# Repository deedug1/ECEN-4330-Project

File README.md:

# ECEN 4330 Project
Files for ECEN 4330 Project

### Source code
All source code is contained in *main_c.c*.

### PCB design files
Schematics and Board files for the PCB can be found under the *Schematics* folder.

### Documentation
Documentation of the project goals and procedures can be found in the PDF labeled *JustinPachlProjectPaper.PDF*.

*University of Nebraska Lincoln*
*Department of Electrical and Computer Engineering (ECE)*

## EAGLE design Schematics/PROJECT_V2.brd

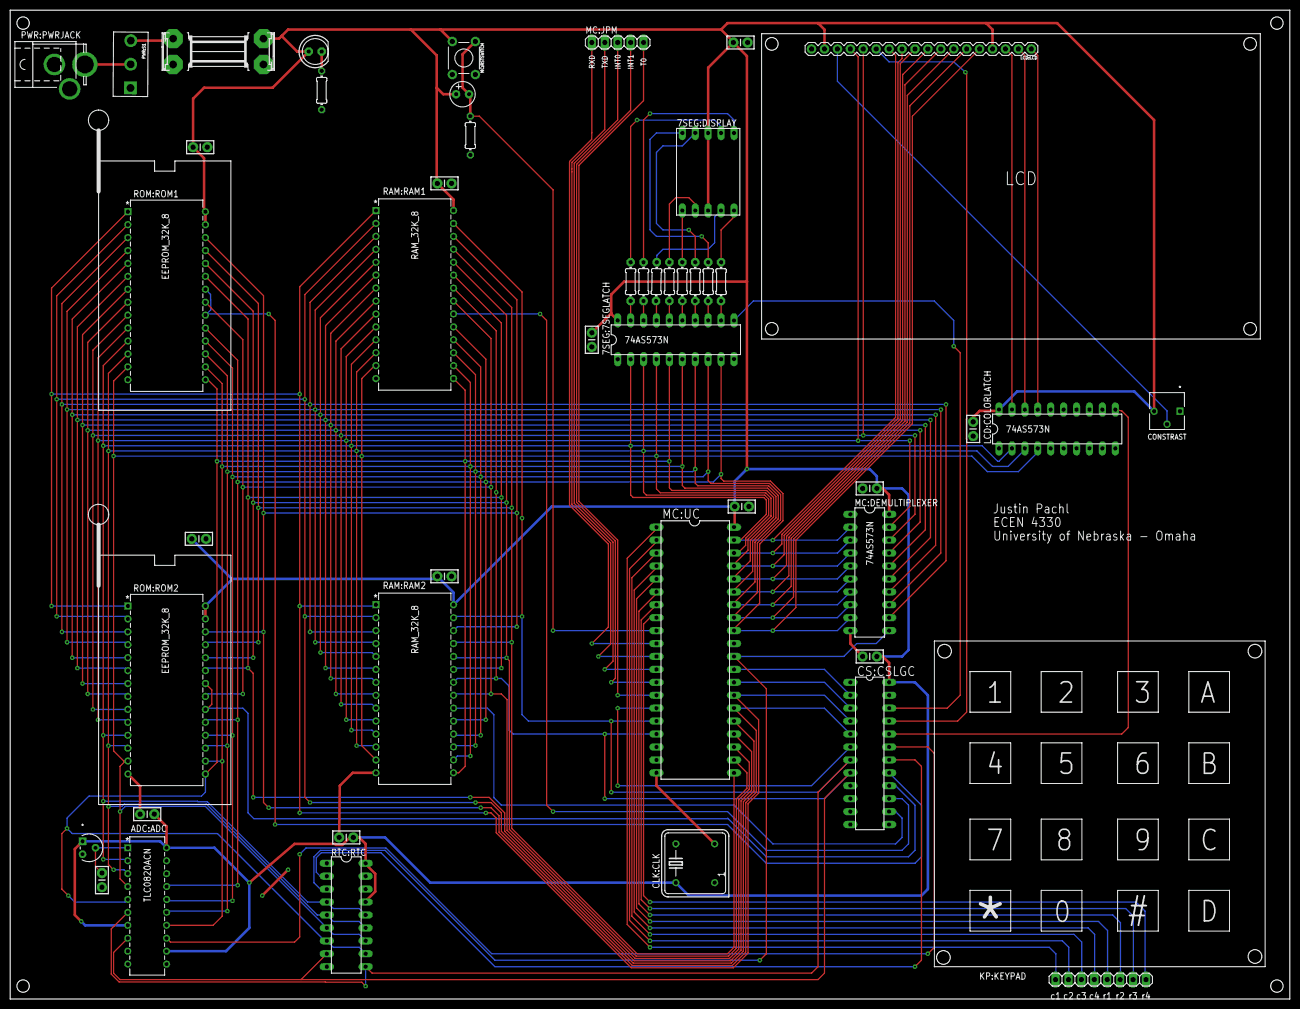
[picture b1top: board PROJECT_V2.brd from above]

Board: 2 copper layers, 251.5 x 194.3 mm, 47 parts (0 on the bottom side), 79 nets.

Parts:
7SEG:7SEGLATCH: 74AS573N; DIL20
7SEG:C1: 0.1uF; CAP-PTH-SMALL-KIT
7SEG:DISPLAY: 7_SEG; 754-1460-5-ND
7SEG:R2, 7SEG:R3, 7SEG:R4, 7SEG:R5, 7SEG:R6, 7SEG:R7, 7SEG:R8, 7SEG:R9: 330; 0204/7
ADC:ADC: TLC0820ACN; N20
ADC:C1, ADC:C2: 0.1uF; CAP-PTH-SMALL-KIT
ADC:TEMPSENS: TEMP_SENSOR; T_3
CLK:CLK: XC269-ND; DIL08S
CS:C1: 0.1uF; CAP-PTH-SMALL-KIT
CS:CSLGC: GAL22V10D; DIL24-3
KP:KEYPAD: KEYPAD4X4
LCD:C1, LCD:C2: 0.1uF; CAP-PTH-SMALL-KIT
LCD:COLORLATCH: 74AS573N; DIL20
LCD:LCD: 1528-1508-ND; 1X18
LCD:R10: 3362P-1-103LF_POT; POT_3362P
MC:C2, MC:C3: 0.1uF; CAP-PTH-SMALL-KIT
MC:DEMULTIPLEXER: 74AS573N; DIL20
MC:JPM: 1X05
MC:R1: 8.2k; 0204/7
MC:RSTSWITCH: MOMENTARY-SWITCH-SPST-PTH-6.0MM; TACTILE_SWITCH_PTH_6.0MM
MC:U$1: 10UF; POL_5MIL
MC:UC: 8051P; DIL40
PWR:PWRFUSE: 2.5A; SHK20Q
PWR:PWRJACK: 2.1mm; SPC4077
PWR:PWRLED: LED5MM
PWR:R11: 1k; 0204/7
PWR:S1: SPDT_EG2355-ND
RAM:C1, RAM:C2: 0.1uF; CAP-PTH-SMALL-KIT
RAM:RAM1, RAM:RAM2: RAM_32K_8; 28P6
ROM:C1, ROM:C2: 0.1uF; CAP-PTH-SMALL-KIT
ROM:ROM1, ROM:ROM2: EEPROM_32K_8; 28_P6
RTC:C1: 0.1uF; CAP-PTH-SMALL-KIT
RTC:RTC: RTC-72421; DIL18

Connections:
7SEG:N$3: 7SEG:7SEGLATCH.19, 7SEG:R2.1
7SEG:N$4: 7SEG:7SEGLATCH.18, 7SEG:R3.1
7SEG:N$5: 7SEG:7SEGLATCH.17, 7SEG:R4.1
7SEG:N$6: 7SEG:7SEGLATCH.16, 7SEG:R5.1
7SEG:N$7: 7SEG:7SEGLATCH.15, 7SEG:R6.1
7SEG:N$8: 7SEG:7SEGLATCH.14, 7SEG:R7.1
7SEG:N$9: 7SEG:7SEGLATCH.13, 7SEG:R8.1
7SEG:N$10: 7SEG:DISPLAY.10, 7SEG:R8.2
7SEG:N$11: 7SEG:DISPLAY.9, 7SEG:R7.2
7SEG:N$12: 7SEG:DISPLAY.1, 7SEG:R6.2
7SEG:N$13: 7SEG:DISPLAY.2, 7SEG:R5.2
7SEG:N$14: 7SEG:DISPLAY.4, 7SEG:R4.2
7SEG:N$33: 7SEG:DISPLAY.6, 7SEG:R3.2
7SEG:N$43: 7SEG:DISPLAY.7, 7SEG:R2.2
7SEG:N$44: 7SEG:DISPLAY.5, 7SEG:R9.2
7SEG:N$45: 7SEG:7SEGLATCH.12, 7SEG:R9.1
7SEGCSWR: 7SEG:7SEGLATCH.11, CS:CSLGC.22
A0: LCD:LCD.4, MC:DEMULTIPLEXER.19, RAM:RAM1.10, RAM:RAM2.10, ROM:ROM1.10, ROM:ROM2.10
A1: LCD:LCD.5, MC:DEMULTIPLEXER.18, RAM:RAM1.9, RAM:RAM2.9, ROM:ROM1.9, ROM:ROM2.9
A2: MC:DEMULTIPLEXER.17, RAM:RAM1.8, RAM:RAM2.8, ROM:ROM1.8, ROM:ROM2.8
A3: MC:DEMULTIPLEXER.16, RAM:RAM1.7, RAM:RAM2.7, ROM:ROM1.7, ROM:ROM2.7
A4: MC:DEMULTIPLEXER.15, RAM:RAM1.6, RAM:RAM2.6, ROM:ROM1.6, ROM:ROM2.6
A5: MC:DEMULTIPLEXER.14, RAM:RAM1.5, RAM:RAM2.5, ROM:ROM1.5, ROM:ROM2.5
A6: MC:DEMULTIPLEXER.13, RAM:RAM1.4, RAM:RAM2.4, ROM:ROM1.4, ROM:ROM2.4
A7: MC:DEMULTIPLEXER.12, RAM:RAM1.3, RAM:RAM2.3, ROM:ROM1.3, ROM:ROM2.3
A8: MC:UC.21, RAM:RAM1.25, RAM:RAM2.25, ROM:ROM1.25, ROM:ROM2.25
A9: MC:UC.22, RAM:RAM1.24, RAM:RAM2.24, ROM:ROM1.24, ROM:ROM2.24
A10: MC:UC.23, RAM:RAM1.21, RAM:RAM2.21, ROM:ROM1.21, ROM:ROM2.21
A11: MC:UC.24, RAM:RAM1.23, RAM:RAM2.23, ROM:ROM1.23, ROM:ROM2.23
A12: MC:UC.25, RAM:RAM1.2, RAM:RAM2.2, ROM:ROM1.2, ROM:ROM2.2
A13: CS:CSLGC.5, MC:UC.26, RAM:RAM1.26, RAM:RAM2.26, ROM:ROM1.26, ROM:ROM2.26
A14: CS:CSLGC.4, MC:UC.27, RAM:RAM1.1, RAM:RAM2.1, ROM:ROM1.1, ROM:ROM2.1
A15: CS:CSLGC.3, MC:UC.28
ADC:N$26: ADC:ADC.1, ADC:C2.1, ADC:TEMPSENS.2
ADCCS: ADC:ADC.13, CS:CSLGC.19
ALE: MC:DEMULTIPLEXER.11, MC:UC.30, RTC:RTC.3
COLORCS: CS:CSLGC.20, LCD:COLORLATCH.11
D0: 7SEG:7SEGLATCH.2, ADC:ADC.2, LCD:COLORLATCH.2, LCD:LCD.7, MC:DEMULTIPLEXER.2, MC:UC.39, RAM:RAM1.11, RAM:RAM2.11, ROM:ROM1.11, ROM:ROM2.11, RTC:RTC.4, RTC:RTC.14
D1: 7SEG:7SEGLATCH.3, ADC:ADC.3, LCD:COLORLATCH.3, LCD:LCD.8, MC:DEMULTIPLEXER.3, MC:UC.38, RAM:RAM1.12, RAM:RAM2.12, ROM:ROM1.12, ROM:ROM2.12, RTC:RTC.5, RTC:RTC.13
D2: 7SEG:7SEGLATCH.4, ADC:ADC.4, LCD:COLORLATCH.4, LCD:LCD.9, MC:DEMULTIPLEXER.4, MC:UC.37, RAM:RAM1.13, RAM:RAM2.13, ROM:ROM1.13, ROM:ROM2.13, RTC:RTC.6, RTC:RTC.12
D3: 7SEG:7SEGLATCH.5, ADC:ADC.5, LCD:LCD.10, MC:DEMULTIPLEXER.5, MC:UC.36, RAM:RAM1.15, RAM:RAM2.15, ROM:ROM1.15, ROM:ROM2.15, RTC:RTC.7, RTC:RTC.11
D4: 7SEG:7SEGLATCH.6, ADC:ADC.14, LCD:LCD.11, MC:DEMULTIPLEXER.6, MC:UC.35, RAM:RAM1.16, RAM:RAM2.16, ROM:ROM1.16, ROM:ROM2.16
D5: 7SEG:7SEGLATCH.7, ADC:ADC.15, LCD:LCD.12, MC:DEMULTIPLEXER.7, MC:UC.34, RAM:RAM1.17, RAM:RAM2.17, ROM:ROM1.17, ROM:ROM2.17
D6: 7SEG:7SEGLATCH.8, ADC:ADC.16, LCD:LCD.13, MC:DEMULTIPLEXER.8, MC:UC.33, RAM:RAM1.18, RAM:RAM2.18, ROM:ROM1.18, ROM:ROM2.18
D7: 7SEG:7SEGLATCH.9, ADC:ADC.17, LCD:LCD.14, MC:DEMULTIPLEXER.9, MC:UC.32, RAM:RAM1.19, RAM:RAM2.19, ROM:ROM1.19, ROM:ROM2.19
GND: 7SEG:7SEGLATCH.1, 7SEG:7SEGLATCH.10, 7SEG:C1.2, ADC:ADC.10, ADC:ADC.11, ADC:C1.2, ADC:C2.2, ADC:TEMPSENS.3, CLK:CLK.4, CS:C1.2, CS:CSLGC.12, LCD:C1.2, LCD:C2.2, LCD:COLORLATCH.1, LCD:COLORLATCH.10, LCD:LCD.1, LCD:R10.1, MC:C2.2, MC:C3.2, MC:DEMULTIPLEXER.1, MC:DEMULTIPLEXER.10, MC:R1.1, MC:UC.20, MC:UC.31, PWR:PWRJACK.1, PWR:PWRJACK.2, PWR:R11.1, RAM:C1.2, RAM:C2.2, RAM:RAM1.14, RAM:RAM2.14, ROM:C1.2, ROM:C2.2, ROM:ROM1.14, ROM:ROM2.14, RTC:C1.2, RTC:RTC.9
LCD:N$16: LCD:LCD.3, LCD:R10.2
LCD:N$17: LCD:COLORLATCH.19, LCD:LCD.16
LCD:N$23: LCD:COLORLATCH.18, LCD:LCD.17
LCD:N$24: LCD:COLORLATCH.17, LCD:LCD.18
LCDCS: CS:CSLGC.21, LCD:LCD.6
MC:INT0: MC:JPM.3, MC:UC.12
MC:INT1: MC:JPM.4, MC:UC.13
MC:N$15: MC:R1.2, MC:RSTSWITCH.1, MC:U$1.2, MC:UC.9
MC:RXD: MC:JPM.1, MC:UC.10
MC:T0: MC:JPM.5, MC:UC.14
MC:TXD: MC:JPM.2, MC:UC.11
unnamed: CLK:CLK.5, MC:UC.19
P3.5: CS:CSLGC.6, MC:UC.15
PONE0: KP:KEYPAD.1, MC:UC.1
PONE1: KP:KEYPAD.2, MC:UC.2
PONE2: KP:KEYPAD.3, MC:UC.3
PONE3: KP:KEYPAD.4, MC:UC.4
PONE4: KP:KEYPAD.5, MC:UC.5
PONE5: KP:KEYPAD.6, MC:UC.6
PONE6: KP:KEYPAD.7, MC:UC.7
PONE7: KP:KEYPAD.8, MC:UC.8
PSEN: CS:CSLGC.2, MC:UC.29
PWR:N$2: PWR:PWRFUSE.1A, PWR:S1.3
PWR:N$48: PWR:PWRJACK.3, PWR:S1.2
PWR:N$49: PWR:PWRLED.K, PWR:R11.2
RAM1CS: CS:CSLGC.15, RAM:RAM1.20
RAM2CS: CS:CSLGC.14, RAM:RAM2.20
RD: ADC:ADC.8, CS:CSLGC.8, MC:UC.17, RAM:RAM1.22, RAM:RAM2.22, RTC:RTC.8
ROM1CS: CS:CSLGC.17, ROM:ROM1.20, ROM:ROM1.22
ROM2CS: CS:CSLGC.16, ROM:ROM2.20, ROM:ROM2.22
RTCCS: CS:CSLGC.18, RTC:RTC.2
VCC: 7SEG:7SEGLATCH.20, 7SEG:C1.1, 7SEG:DISPLAY.3, 7SEG:DISPLAY.8, ADC:ADC.7, ADC:ADC.12, ADC:ADC.20, ADC:C1.1, ADC:TEMPSENS.1, CLK:CLK.8, CS:C1.1, CS:CSLGC.24, LCD:C1.1, LCD:C2.1, LCD:COLORLATCH.20, LCD:LCD.2, LCD:LCD.15, LCD:R10.3, MC:C2.1, MC:C3.1, MC:DEMULTIPLEXER.20, MC:RSTSWITCH.3, MC:U$1.1, MC:UC.40, PWR:PWRFUSE.2A, PWR:PWRLED.A, RAM:C1.1, RAM:C2.1, RAM:RAM1.28, RAM:RAM2.28, ROM:C1.1, ROM:C2.1, ROM:ROM1.27, ROM:ROM1.28, ROM:ROM2.27, ROM:ROM2.28, RTC:C1.1, RTC:RTC.15, RTC:RTC.18
WR: ADC:ADC.6, CS:CSLGC.7, MC:UC.16, RAM:RAM1.27, RAM:RAM2.27, RTC:RTC.10

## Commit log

2018-03-04 Wrote keyscan/ascii
2018-03-04 Wrote tasks and 7seg interactions
2018-03-04 Added schematic
2018-03-04 Added chip select logic
2018-03-04 Added Keypad config, fixed bug where 7 would always dispaly on segment device
2018-03-05 Fixed bug where 7 would always write
2018-03-05 Added startup sequence and fixed state change bug
2018-03-05 Actually fixed bugs
2018-03-07 Matched schematic with current breadboard config
2018-03-09 Pre merge commit
2018-03-10 Added LCD Circuit, Changed R/W Pin, Started ADC Circuit
2018-03-10 Modified chip select to put R_W high or low dependent on edge of RD or WR, Change LCDCS to go high when LCD module is selected
2018-03-10 Added RTC circuit
2018-03-10 Reverted chip_select, Fixed latch bug in schematic
2018-03-11 Added ADC to schematic, fixed other various 573 issues, Added LCD interfacing code to main
2018-03-11 Added RTC, LCD, ADC Code
2018-03-12 Changed lbr to more clearly display specific parts, Added Color select to schematic
2018-03-12 Removed redundant functions for RTC, changed some function names to better represent the action better, Modified RTC schematic to be more informative
2018-03-12 Added Color select interfacing
2018-03-12 Added color capabilities to code NOTE:BUGGED
2018-03-13 Started adding power circuit, changed switch to match footprint, started debugging RTC bug
2018-03-14 Final design before hierarchiel block
2018-03-14 Added hierarchy sheet
2018-03-15 Started board, fixed ERC issues
2018-03-19 Added bypass capacitors to schematic
2018-03-19 Started routing pcb, Fixed some mistakes on the schematic, added note for BCD converter in code.
2018-03-20 I made updates to the board and pcb not sure what exactly nothing major
2018-03-20 Changed pinout to match current schematic
2018-03-20 Continued working on traces for signals, changed output of chip_select
2018-03-20 Continued trace work.
2018-03-21 Finished routing still needs cleanup
2018-03-21 Double checked connections against breadboard prototype fixed connection issues
2018-03-24 Did a lot of clean up work move the lcd down some to make the mounting holes not so close
2018-03-24 Added name fixed some small board problems
2018-04-03 Finalized board, finalized schematic, fixed bugs in cs
2018-04-04 Added some C things, Fixed bug in main.asm that prevent LCD Dest switching
2018-04-05 Cleaned up directories, reverted main.asm
2018-04-06 Removed old junk fixed some dptr bugs
2018-04-06 Added TEST for ram, as well as display uptime and temperature in celsius
2018-04-06 Added variable delay function Fixed load Update loading character
2018-04-06 Seperated source into seperate files for easier to read fixed stuff
2018-04-06 Fixed Delay_xms made sure src complied still needs testing
2018-04-06 Made seperate files for hardware interfacing libs
2018-04-07 Startd writing C code
2018-04-10 Added a ton of C code... should not have added this much without committing my b
2018-04-11 Added state machine work fixed multiple bugs
2018-04-11 Finished coding Memory functions still needs cleanup
2018-04-13 Added fill program
2018-04-17 Fixed some small bugs, cleaned up some text, created print address/print byte
2018-04-18 Fixed compilation issue with printf_tiny
2018-04-21 Fixed some bugs in search, added confirmation message at input
2018-04-23 Modfied loops on fill and move to move the proper amount of values entered by the user
2018-05-02 Unknown chnages made for presentation
2018-06-03 Added git ignore, cleaned up some files, commited project paper (ECEN 4330 Final Paper.pdf), added adjuted bom
2018-06-03 updated paper
2018-06-04 PDF correction
2018-09-07 Removed assembly files, fixed compile batch file.
2018-09-07 Added first revision of buad functions
2018-09-08 Implemented most Serial functions still need good serial program
2018-09-08 Added very sloppy serail stuff
2018-09-11 I fucked up but this should work
2018-09-15 Just double checking

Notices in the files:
parts and their libraries:
SparkFun-Switches: Licensing: Creative Commons ShareAlike 4.0 International - https://creativecommons.org/licenses/by-sa/4.0
